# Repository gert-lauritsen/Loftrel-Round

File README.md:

# Loftrelæ Round

Round ceiling-mounted relay module with ESP8266/Home Assistant integration, AC sense input, relay output, KiCad PCB files, LTspice simulation files, Gerber production files, interactive BOM, and 3D-printable enclosure files.

> **Warning — mains voltage**
>
> This project is intended for work around 230 VAC mains wiring. Only build, test, or install it if you are qualified to work on mains-powered equipment and understand local electrical regulations. Always isolate power before touching the circuit. Use correct fusing, creepage, clearance, strain relief, enclosure material, and certified installation practices. The repository files are design files and do not by themselves make the product certified for permanent installation.

# Mini Version

Mini version is for buildin. It does the same, just in a smaller version.

---

## Project purpose

`Loftrelæ Round` is designed as a compact round relay module for ceiling installation. It is intended to fit into a round ceiling bracket or ceiling-mounted housing.

The module connects to:

- **P / phase / live**
- **N / neutral**
- **M1 / switched or sense input**

The sense input is used to monitor whether the original wall switch or local switch has been activated. The ESP8266 firmware publishes the relay state and sense state to Home Assistant by MQTT, so the original physical switch can still be used while Home Assistant can monitor and control the relay.

---

## Repository structure

```text
Loftrel-Round/
├── ACMonitorHA/
│   └── ACMonitorHA.ino              # ESP8266 firmware
├── PCB/
│   ├── LoftRelayRoundGerber/        # Gerber + drill files for PCB production
│   ├── Simulation/                  # LTspice zero-detect simulation
│   ├── bom/
│   │   └── ibom.html                # Interactive HTML BOM
│   ├── ESP8266.kicad_sch            # ESP8266 schematic sheet
│   ├── loftrelayRound.kicad_pro     # KiCad project
│   ├── loftrelayRound.kicad_sch     # Main KiCad schematic
│   ├── loftrelayRound.kicad_pcb     # KiCad PCB layout
│   └── loftrelayRound.pdf           # Schematic PDF export
├── Rund Print 3D/
│   ├── Lys Driver.stl
│   ├── Lys Driver Låg.stl
│   └── Lys Driver Låg 2mm.stl
└── README.md
```

---

## Main features

- Round ceiling relay PCB format.
- ESP8266 / ESP-12E based controller.
- MQTT integration with Home Assistant.
- Home Assistant MQTT discovery.
- Relay output on GPIO15.
- AC/switch sense input through:
  - analog ADC level on A0
  - digital state on GPIO5
- Status LED on GPIO2.
- MQTT availability topic.
- Separate MQTT event topic for toggle/state-change handling.
- KiCad schematic, PCB layout, Gerber production output, drill files, simulation files, and 3D-printable enclosure parts.

---

## Hardware overview

### Functional blocks

```text
230 VAC input
   │
   ├── Power supply section
   │      └── Provides low-voltage supply for ESP8266 and relay electronics
   │
   ├── Relay switching section
   │      └── Controlled by ESP8266 GPIO15
   │
   ├── AC / switch sense section
   │      ├── Analog sense to ESP8266 A0
   │      └── Digital sense to ESP8266 GPIO5
   │
   └── ESP8266 controller
          ├── Wi-Fi
          ├── MQTT
          ├── Home Assistant discovery
          ├── GPIO2 LED
          └── GPIO15 relay output
```

### Important ESP8266 pin assignments

| ESP8266 pin | Function | Notes |
|---|---|---|
| A0 | Analog AC/sense level | Used for threshold + hysteresis detection |
| GPIO5 | Digital AC/sense input | Published as binary sensor |
| GPIO2 | Status LED | Often active-low on ESP8266 boards |
| GPIO15 | Relay output | Must be compatible with ESP8266 boot requirements |
| 3V3 | Logic supply | Stable 3.3 V required |
| GND | Logic ground | Low-voltage reference |

### ADC warning

The bare ESP8266/ESP-12E ADC input is normally limited to approximately **0–1.0 V**. Some development boards include a resistor divider and accept a larger input range. The firmware currently uses:

```cpp
const float ADC_FULL_SCALE_V = 3.3;
```

Verify the actual ADC scaling on the PCB before applying a voltage to A0. If the PCB feeds the bare ESP8266 ADC directly, the maximum allowed voltage must not exceed the ESP8266 ADC rating.

---

## Firmware

The firmware is located in:

```text
ACMonitorHA/ACMonitorHA.ino
```

It is written for the Arduino ESP8266 core and uses MQTT for communication with Home Assistant.

### Required Arduino libraries

Install these in Arduino IDE or PlatformIO:

- ESP8266 Arduino core
- `ESP8266WiFi`
- `PubSubClient`

### Configuration file

The firmware includes:

```cpp
#include "secrets.h"
```

Create `ACMonitorHA/secrets.h` locally. Do not commit real Wi-Fi or MQTT credentials.

Example:

```cpp
#pragma once

#define sWIFI_SSID     "YourWiFiSSID"
#define sWIFI_PASS     "YourWiFiPassword"

#define sMQTT_SERVER   "192.168.1.10"
#define sMQTT_USER     "mqtt_user"
#define sMQTT_PASS     "mqtt_password"

// Static IP configuration
#define LOCAL_IP       192,168,1,50
#define GATEWAY_IP     192,168,1,1
#define SUBNET_MASK    255,255,255,0
```

### Core firmware settings

```cpp
const char* DEVICE_ID   = "acmonitorha_01";
const char* DEVICE_NAME = "ACMonitorHA";

const float ADC_FULL_SCALE_V = 3.3;

float LOW_THRESHOLD_V  = 1.3;
float HIGH_THRESHOLD_V = 1.6;

const uint8_t PIN_DIGITAL_AC = 5;   // GPIO5
const uint8_t PIN_LED        = 2;   // GPIO2
const uint8_t PIN_RELAY      = 15;  // GPIO15
```

### MQTT topic layout

Base topic:

```text
acmonitorha/acmonitorha_01
```

Published topics:

| Topic | Purpose | Retained |
|---|---|---|
| `acmonitorha/acmonitorha_01/availability` | Online/offline state | Yes |
| `acmonitorha/acmonitorha_01/state` | JSON state payload | Yes |
| `acmonitorha/acmonitorha_01/event` | JSON toggle counter/event | No |
| `acmonitorha/acmonitorha_01/trigger/ac_toggle` | Simple trigger payload for HA automation | No |
| `acmonitorha/acmonitorha_01/relay/set` | Relay command topic | No |

### Example state payload

```json
{
  "adc_voltage": 1.542,
  "ac_state": "ON",
  "gpio5": "ON",
  "relay": "OFF",
  "low_threshold": 1.30,
  "high_threshold": 1.60
}
```

### Home Assistant MQTT discovery entities

The firmware publishes MQTT discovery for:

| Home Assistant entity | Type | Description |
|---|---|---|
| AC ADC Voltage | Sensor | ADC voltage in volts |
| AC Analog State | Binary sensor | Hysteresis-filtered AC/switch state |
| AC GPIO5 State | Binary sensor | Digital state from GPIO5 |
| AC Relay | Switch | Relay output control |
| AC Toggle Event | Sensor | Counter incremented on analog state change |
| `ac_toggle` | Device automation trigger | Trigger event for automations |

### Home Assistant automation trigger

The device automation trigger listens for:

```text
topic: acmonitorha/acmonitorha_01/trigger/ac_toggle
payload: TOGGLE
```

Example Home Assistant automation using raw MQTT trigger:

```yaml
alias: Loftrelæ Round toggle event
mode: single

trigger:
  - platform: mqtt
    topic: acmonitorha/acmonitorha_01/trigger/ac_toggle
    payload: "TOGGLE"

action:
  - service: light.toggle
    target:
      entity_id: light.example_light
```

If you use Home Assistant MQTT device discovery, the same event can also appear as a device trigger named similar to:

```text
"ac_toggle" pressed
```

---

## Building and flashing the firmware

### Arduino IDE

1. Install the ESP8266 board package.
2. Select an ESP8266/ESP-12E compatible board.
3. Install `PubSubClient`.
4. Create `ACMonitorHA/secrets.h`.
5. Open `ACMonitorHA/ACMonitorHA.ino`.
6. Compile and upload.
7. Open Serial Monitor at `115200 baud`.

### PlatformIO option

A minimal `platformio.ini` can be created as:

```ini
[env:esp12e]
platform = espressif8266
board = esp12e
framework = arduino
monitor_speed = 115200

lib_deps =
    knolleary/PubSubClient
```

---

## Simulation

Simulation files are located in:

```text
PCB/Simulation/
```

Files included:

| File | Description |
|---|---|
| `ZeroDetect.asc` | LTspice schematic for zero/sense detection simulation |
| `ZeroDetect.log` | LTspice simulation log |
| `ZeroDetect.raw` | LTspice waveform result |
| `ZeroDetect.op.raw` | LTspice operating point result |

### Opening the simulation

1. Install LTspice.
2. Open:

```text
PCB/Simulation/ZeroDetect.asc
```

3. Run the simulation.
4. Inspect the generated node voltages and switching/sense waveform.
5. Compare the sense output against the firmware thresholds.

### What to verify in simulation

- The sense voltage stays inside the safe input range for the ESP8266 ADC/GPIO.
- The analog sense voltage provides enough margin around the configured thresholds.
- The digital sense level is compatible with ESP8266 3.3 V logic.
- The waveform does not contain excessive ripple that would cause false toggles.
- The low-voltage side remains isolated or otherwise protected according to the actual hardware design.
- 

---

## PCB design

PCB files are located in:

```text
PCB/
```

Main KiCad files:

| File | Description |
|---|---|
| `loftrelayRound.kicad_pro` | KiCad project |
| `loftrelayRound.kicad_sch` | Main schematic |
| `ESP8266.kicad_sch` | ESP8266 schematic sheet |
| `loftrelayRound.kicad_pcb` | PCB layout |
| `loftrelayRound.pdf` | Schematic PDF export |

Open [Schematic](./PCB/loftrelayRound.pdf) in pdf format

### Opening the PCB project

1. Install KiCad.
2. Open:

```text
PCB/loftrelayRound.kicad_pro
```

3. Inspect schematic and PCB.
4. Run ERC and DRC before manufacturing.
5. Check creepage and clearance manually for 230 VAC areas.

### PCB production files

Gerber and drill files are located in:

```text
PCB/LoftRelayRoundGerber/
```

Included production outputs:

| File | Layer / output |
|---|---|
| `loftrelayRound-F_Cu.gbr` | Front copper |
| `loftrelayRound-B_Cu.gbr` | Back copper |
| `loftrelayRound-F_Mask.gbr` | Front solder mask |
| `loftrelayRound-B_Mask.gbr` | Back solder mask |
| `loftrelayRound-F_Paste.gbr` | Front paste |
| `loftrelayRound-B_Paste.gbr` | Back paste |
| `loftrelayRound-F_Silkscreen.gbr` | Front silkscreen |
| `loftrelayRound-B_Silkscreen.gbr` | Back silkscreen |
| `loftrelayRound-Edge_Cuts.gbr` | Board outline |
| `loftrelayRound-PTH.drl` | Plated through holes |
| `loftrelayRound-NPTH.drl` | Non-plated through holes |

### Recommended PCB checks before ordering

- Verify board diameter and mechanical fit in the intended ceiling enclosure.
- Verify copper-to-copper clearance in mains sections.
- Verify slot/cutout dimensions if used for isolation.
- Verify terminal block footprints and wire entry direction.
- Verify relay footprint and coil/contact ratings.
- Verify ESP8266 antenna keep-out.
- Verify mounting holes and enclosure interference.
- Verify solder mask expansion and paste layers.
- Load Gerbers in an independent Gerber viewer before ordering.

---

## Interactive BOM

The interactive BOM is located at:

```text
PCB/bom/ibom.html
```

Open it in a browser to identify component placement, values, footprints, and assembly side.

Recommended use:

1. Open `PCB/bom/ibom.html`.
2. Select a component group.
3. Place/solder the highlighted components.
4. Mark them as placed in the iBOM interface.
5. Continue until all components are mounted.

---

## 3D printed enclosure

3D print files are located in:

```text
Rund Print 3D/
```

Included files:

| File | Description |
|---|---|
| `Lys Driver.stl` | Main printed body |
| `Lys Driver Låg.stl` | Lid |
| `Lys Driver Låg 2mm.stl` | Alternative 2 mm lid |

### Printing notes

- Use a material suitable for the installation environment.
- For mains installations, consider flame-retardant material and electrical enclosure requirements.
- Verify fit before installing electronics.
- Ensure adequate insulation and strain relief.
- Ensure that the enclosure cannot be opened without tools if installed near mains wiring.

---

## Installation concept

Typical installation concept:

```text
230 VAC supply
   ├── P / live  ──────── PCB P input
   ├── N / neutral ────── PCB N input
   └── Switched input ─── PCB M1 / sense input

PCB relay output
   └── Load / lamp / driver input
```

The actual wiring depends on the relay contact arrangement and the local installation. Check the schematic and relay contact rating before connecting any load.

---

## Commissioning checklist

Before applying mains power:

- [ ] Inspect all solder joints.
- [ ] Verify no solder bridges.
- [ ] Check polarity of capacitors, diodes, regulator, relay driver, and ESP8266 module.
- [ ] Check mains and low-voltage isolation distance.
- [ ] Check continuity between expected nets.
- [ ] Check there is no short between live and neutral.
- [ ] Check there is no short between mains side and low-voltage side unless intentionally designed.
- [ ] Verify enclosure fit.
- [ ] Verify relay contact rating.
- [ ] Verify fuse/protection if applicable.
- [ ] Verify `secrets.h` configuration.
- [ ] Flash firmware before final installation.
- [ ] Test first with current-limited or isolated setup if possible.

After applying power:

- [ ] Confirm 3.3 V supply.
- [ ] Confirm ESP8266 boots.
- [ ] Confirm Wi-Fi connection.
- [ ] Confirm MQTT availability topic becomes `online`.
- [ ] Confirm Home Assistant discovery entities appear.
- [ ] Confirm ADC voltage is realistic.
- [ ] Confirm GPIO5 state changes as expected.
- [ ] Confirm relay can be switched from Home Assistant.
- [ ] Confirm physical switch/sense input creates a toggle event.
- [ ] Confirm relay output works with the intended load.

---

## Troubleshooting

### Device does not appear in Home Assistant

Check:

- MQTT broker IP, user, and password.
- Wi-Fi SSID and password.
- `DEVICE_ID` uniqueness.
- Home Assistant MQTT integration is enabled.
- MQTT discovery is enabled in Home Assistant.
- ESP8266 serial output at `115200 baud`.

### Toggle event appears as sensor activity but automation does not trigger

Check that the firmware publishes the simple trigger payload:

```text
topic: acmonitorha/acmonitorha_01/trigger/ac_toggle
payload: TOGGLE
```

The JSON event topic and the trigger topic should be separate:

```text
/event                 -> JSON counter/log event
/trigger/ac_toggle     -> simple TOGGLE payload
```

### ADC value is wrong

Check:

- `ADC_FULL_SCALE_V`
- resistor divider values
- actual ESP8266 board/module ADC range
- whether A0 is connected to bare ESP8266 ADC or a development-board divider
- ripple/noise on the sense signal

### Relay does not switch

Check:

- GPIO15 boot requirement and output state.
- Relay driver transistor/MOSFET orientation.
- Flyback diode orientation.
- Relay coil voltage.
- Relay supply voltage.
- MQTT command topic:

```text
acmonitorha/acmonitorha_01/relay/set
```

Payload must be:

```text
ON
```

or:

```text
OFF
```

---

## Development notes

Suggested future improvements:

- Add a `platformio.ini`.
- Add schematic and PCB screenshots to the README.
- Add Gerber preview images.
- Add iBOM screenshot.
- Add enclosure render images.
- Add a wiring diagram.
- Add release ZIP containing Gerbers, BOM, schematic PDF, and firmware source.
- Add version number to firmware and MQTT state payload.
- Add retained config cleanup instructions for MQTT discovery changes.
- Add OTA update support.
- Add configurable thresholds through MQTT or Home Assistant number entities.

---

## License

No license file is currently described here. Add a `LICENSE` file if the project is intended for reuse, modification, or distribution.

---

## Disclaimer

This is a DIY electronics project involving mains voltage. The author and contributors are not responsible for damage, injury, fire, code violations, or unsafe installations. Verify the design, PCB, enclosure, wiring, component ratings, firmware behavior, and local electrical requirements before use.

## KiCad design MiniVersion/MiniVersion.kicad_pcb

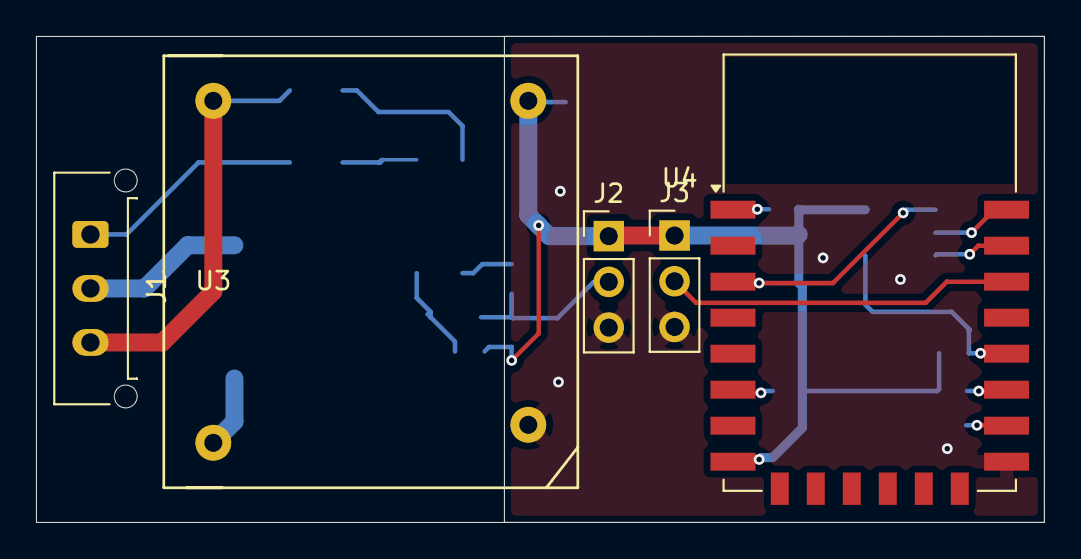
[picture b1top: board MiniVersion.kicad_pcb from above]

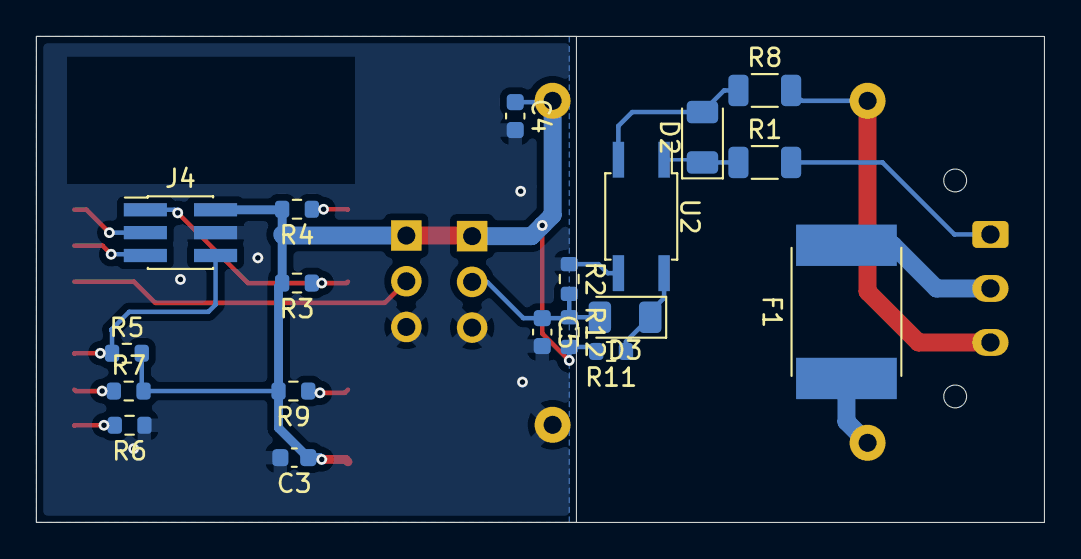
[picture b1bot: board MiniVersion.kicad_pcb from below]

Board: 2 copper layers, 56.0 x 27.0 mm, 24 parts (19 on the bottom side), 19 nets.

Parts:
C3, C4: 1uF; C_0603_1608Metric
C5: 2u2; C_0603_1608Metric
D2, D3: D; D_1206_3216Metric
F1: 8A; Fuse_SMD2920
J1: PowerIn; Molex_Micro-Fit_3.0_43650-0315_1x03_P3.00mm_Vertical
J2, J3: Conn_01x03; PinHeader_1x03_P2.54mm_Vertical
J4: Program; PinHeader_2x03_P1.27mm_Vertical_SMD
R1, R8: 100k; R_1206_3216Metric
R2: 1M; R_0603_1608Metric
R3, R4, R5, R6, R7, R9: 10k; R_0603_1608Metric
R11, R12: 100k; R_0603_1608Metric
U2: LTV-355T; SO-4_4.4x3.6mm_Pitch2.54mm
U3: VTX-214-003-203; Vigortronix3W
U4: ESP-12E

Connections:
+3V3: C3.1, C4.1, J2.1, J3.1, J4.2, R3.2, R4.2, R5.2, R7.2, R9.2, R11.2, R12.2, U3.2 (VCC), U4.8 (VCC)
/ESP8266/D0: J4.6, R5.1, U4.18 (GPIO0)
/ESP8266/D2: R7.1, U4.17 (GPIO2)
/ESP8266/D5: J3.2, U4.20 (GPIO5)
/ESP8266/D12: R9.1, U4.6 (GPIO12)
/ESP8266/D15: R6.2, U4.16 (GPIO15)
/ESP8266/EN: J4.1, R3.1, U4.3 (EN)
/ESP8266/RX: J4.5, U4.21 (GPIO3/RXD)
/ESP8266/TX: J4.3, U4.22 (GPIO1/TXD)
/Opto: C5.1, D3.2 (A), J2.2, R2.2, R12.1
GND: C3.2, C4.2, C5.2, J2.3, J3.3, J4.4, R2.1, R6.1, U2.3, U3.1 (GND), U4.15 (GND)
unnamed: D2.2 (A), R8.1, U2.2
unnamed: D2.1 (K), R1.1, U2.1
unnamed: D3.1 (K), R11.1, U2.4
unnamed: J1.1, R1.2
unnamed: F1.2, J1.2
unnamed: J1.3, R8.2, U3.3 (N)
unnamed: F1.1, U3.4 (L)
unnamed: R4.1, U4.1 (~RST)

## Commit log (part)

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2020-03-16 Init
2020-05-02 Code fungere
2020-05-02 Diagram rettet til
    Minimeret, så overflødige komponenter er fjernet
2020-09-14 Kasse 3D
2026-05-27 change in sensor, made for HA
2026-05-28 Miniversion
